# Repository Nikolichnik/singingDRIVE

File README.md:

# singingDRIVE
<h4>Old CD-ROM drive re purposed to sing.</h4>

It includes stepper motor driver controlled by Arduino microntroller. Video demo available <a href="https://www.youtube.com/watch?v=EQ7sJ51bUXY"><em>here</em></a> or you can just click image below.

<hr>

<p align="center">
  
</p>

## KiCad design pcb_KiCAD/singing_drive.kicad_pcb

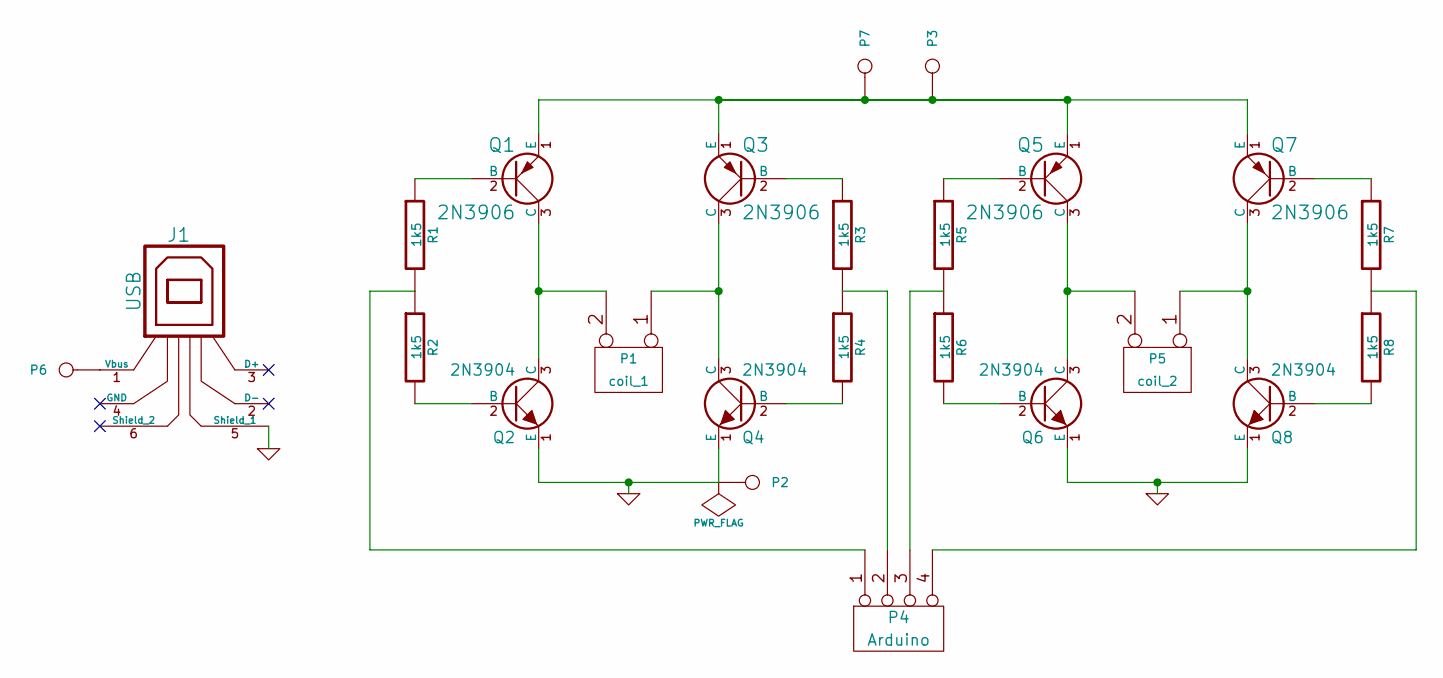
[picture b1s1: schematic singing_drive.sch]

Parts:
J1: USB
P1: coil_1
P2, P3, P6, P7: CONN_1
P4: Arduino
P5: coil_2
Q1, Q3, Q5, Q7: 2N3906
Q2, Q4, Q6, Q8: 2N3904
R1, R2, R3, R4, R5, R6, R7, R8: 1k5

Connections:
GND: J1.5 (Shield_1), P2.1, Q2.1 (E), Q4.1 (E), Q6.1 (E), Q8.1 (E)
unnamed: P4.1, R1.2, R2.1
unnamed: P4.4, R7.2, R8.1
unnamed: P4.3, R5.2, R6.1
unnamed: P4.2, R3.2, R4.1
unnamed: Q8.2 (B), R8.2
unnamed: Q7.2 (B), R7.1
unnamed: P5.1, Q7.3 (C), Q8.3 (C)
unnamed: P5.2 (PM), Q5.3 (C), Q6.3 (C)
unnamed: Q5.2 (B), R5.1
unnamed: Q6.2 (B), R6.2
unnamed: J1.1 (Vbus), P6.1
unnamed: P3.1, P7.1, Q1.1 (E), Q3.1 (E), Q5.1 (E), Q7.1 (E)
unnamed: Q1.2 (B), R1.1
unnamed: Q2.2 (B), R2.2
unnamed: P1.2 (PM), Q1.3 (C), Q2.3 (C)
unnamed: Q4.2 (B), R4.2
unnamed: Q3.2 (B), R3.1
unnamed: P1.1, Q3.3 (C), Q4.3 (C)

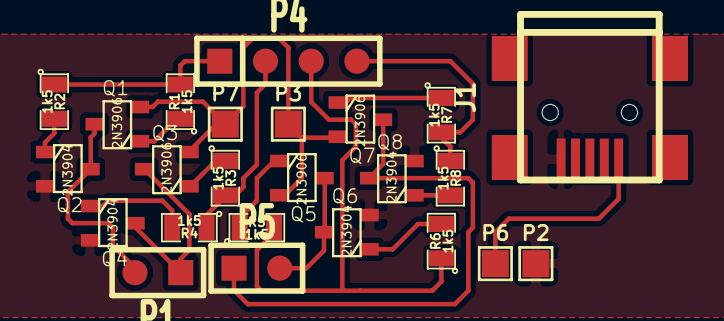
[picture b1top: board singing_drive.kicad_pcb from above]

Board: 2 copper layers, 24 parts (0 on the bottom side), 19 nets.
